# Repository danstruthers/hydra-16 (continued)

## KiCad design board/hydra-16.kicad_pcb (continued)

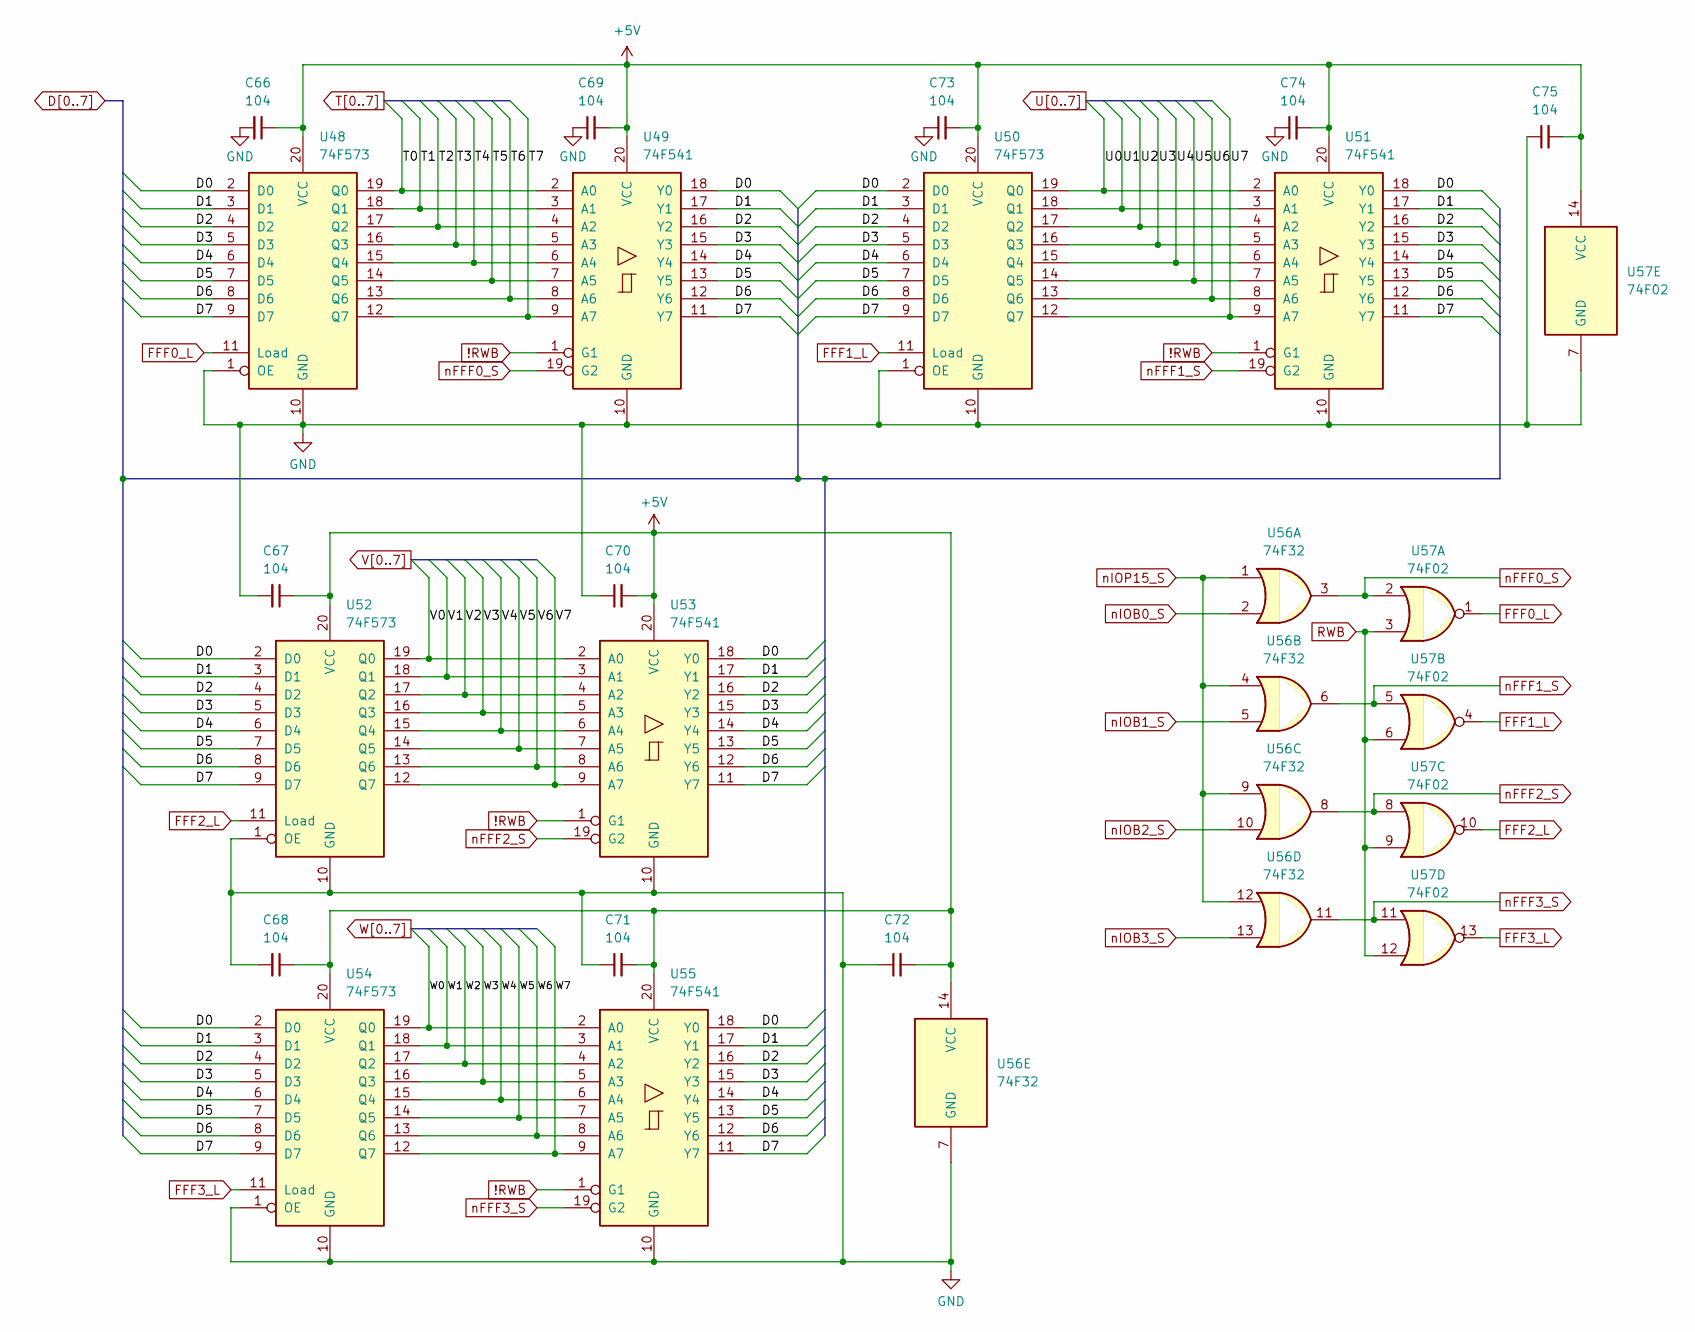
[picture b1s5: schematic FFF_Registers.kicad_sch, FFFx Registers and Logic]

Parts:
C66, C67, C68, C69, C70, C71, C72, C73, C74, C75: 104; C_Disc_D5.0mm_W2.5mm_P5.00mm
U48, U50, U52, U54: 74F573; DIP-20_W7.62mm_Socket_LongPads
U49, U51, U53, U55: 74F541; DIP-20_W7.62mm_Socket_LongPads
U56: 74F32; DIP-14_W7.62mm_Socket_LongPads
U57: 74F02; DIP-14_W7.62mm_Socket_LongPads

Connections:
!RWB: U49.1 (G1), U51.1 (G1), U53.1 (G1), U55.1 (G1); also elsewhere on the board
+5V: C66.1, C67.1, C68.1, C69.2, C70.2, C71.2, C72.2, C73.2, C74.2, C75.2, U48.20 (VCC), U49.20 (VCC), U50.20 (VCC), U51.20 (VCC), U52.20 (VCC), U53.20 (VCC), U54.20 (VCC), U55.20 (VCC), U56.14 (VCC), U57.14 (VCC); also elsewhere on the board
D0: U48.2 (D0), U49.18 (Y0), U50.2 (D0), U51.18 (Y0), U52.2 (D0), U53.18 (Y0), U54.2 (D0), U55.18 (Y0); also elsewhere on the board
D1: U48.3 (D1), U49.17 (Y1), U50.3 (D1), U51.17 (Y1), U52.3 (D1), U53.17 (Y1), U54.3 (D1), U55.17 (Y1); also elsewhere on the board
D2: U48.4 (D2), U49.16 (Y2), U50.4 (D2), U51.16 (Y2), U52.4 (D2), U53.16 (Y2), U54.4 (D2), U55.16 (Y2); also elsewhere on the board
D3: U48.5 (D3), U49.15 (Y3), U50.5 (D3), U51.15 (Y3), U52.5 (D3), U53.15 (Y3), U54.5 (D3), U55.15 (Y3); also elsewhere on the board
D4: U48.6 (D4), U49.14 (Y4), U50.6 (D4), U51.14 (Y4), U52.6 (D4), U53.14 (Y4), U54.6 (D4), U55.14 (Y4); also elsewhere on the board
D5: U48.7 (D5), U49.13 (Y5), U50.7 (D5), U51.13 (Y5), U52.7 (D5), U53.13 (Y5), U54.7 (D5), U55.13 (Y5); also elsewhere on the board
D6: U48.8 (D6), U49.12 (Y6), U50.8 (D6), U51.12 (Y6), U52.8 (D6), U53.12 (Y6), U54.8 (D6), U55.12 (Y6); also elsewhere on the board
D7: U48.9 (D7), U49.11 (Y7), U50.9 (D7), U51.11 (Y7), U52.9 (D7), U53.11 (Y7), U54.9 (D7), U55.11 (Y7); also elsewhere on the board
FFF0_L: U48.11 (Load), U57.1
FFF1_L: U50.11 (Load), U57.4
FFF2_L: U52.11 (Load), U57.10
FFF3_L: U54.11 (Load), U57.13
GND: C66.2, C67.2, C68.2, C69.1, C70.1, C71.1, C72.1, C73.1, C74.1, C75.1, U48.1 (OE), U48.10 (GND), U49.10 (GND), U50.1 (OE), U50.10 (GND), U51.10 (GND), U52.1 (OE), U52.10 (GND), U53.10 (GND), U54.1 (OE), U54.10 (GND), U55.10 (GND), U56.7 (GND), U57.7 (GND); also elsewhere on the board
RWB: U57.3, U57.6, U57.9, U57.12; also elsewhere on the board
T0: U48.19 (Q0), U49.2 (A0); also elsewhere on the board
T1: U48.18 (Q1), U49.3 (A1); also elsewhere on the board
T2: U48.17 (Q2), U49.4 (A2); also elsewhere on the board
T3: U48.16 (Q3), U49.5 (A3); also elsewhere on the board
T4: U48.15 (Q4), U49.6 (A4)
T5: U48.14 (Q5), U49.7 (A5)
T6: U48.13 (Q6), U49.8 (A6)
T7: U48.12 (Q7), U49.9 (A7)
U0: U50.19 (Q0), U51.2 (A0); also elsewhere on the board
U1: U50.18 (Q1), U51.3 (A1); also elsewhere on the board
U2: U50.17 (Q2), U51.4 (A2); also elsewhere on the board
U3: U50.16 (Q3), U51.5 (A3); also elsewhere on the board
U4: U50.15 (Q4), U51.6 (A4)
U5: U50.14 (Q5), U51.7 (A5)
U6: U50.13 (Q6), U51.8 (A6)
U7: U50.12 (Q7), U51.9 (A7)
V0: U52.19 (Q0), U53.2 (A0); also elsewhere on the board
V1: U52.18 (Q1), U53.3 (A1); also elsewhere on the board
V2: U52.17 (Q2), U53.4 (A2); also elsewhere on the board
V3: U52.16 (Q3), U53.5 (A3); also elsewhere on the board
V4: U52.15 (Q4), U53.6 (A4)
V5: U52.14 (Q5), U53.7 (A5)
V6: U52.13 (Q6), U53.8 (A6)
V7: U52.12 (Q7), U53.9 (A7)
W0: U54.19 (Q0), U55.2 (A0); also elsewhere on the board
W1: U54.18 (Q1), U55.3 (A1); also elsewhere on the board
W2: U54.17 (Q2), U55.4 (A2); also elsewhere on the board
W3: U54.16 (Q3), U55.5 (A3); also elsewhere on the board
W4: U54.15 (Q4), U55.6 (A4); also elsewhere on the board
W5: U54.14 (Q5), U55.7 (A5); also elsewhere on the board
W6: U54.13 (Q6), U55.8 (A6)
W7: U54.12 (Q7), U55.9 (A7)
nFFF0_S: U49.19 (G2), U56.3, U57.2
nFFF1_S: U51.19 (G2), U56.6, U57.5
nFFF2_S: U53.19 (G2), U56.8, U57.8
nFFF3_S: U55.19 (G2), U56.11, U57.11
nIOB0_S: U56.2; also elsewhere on the board
nIOB1_S: U56.5; also elsewhere on the board
nIOB2_S: U56.10; also elsewhere on the board
nIOB3_S: U56.13; also elsewhere on the board
nIOP15_S: U56.1, U56.4, U56.9, U56.12; also elsewhere on the board

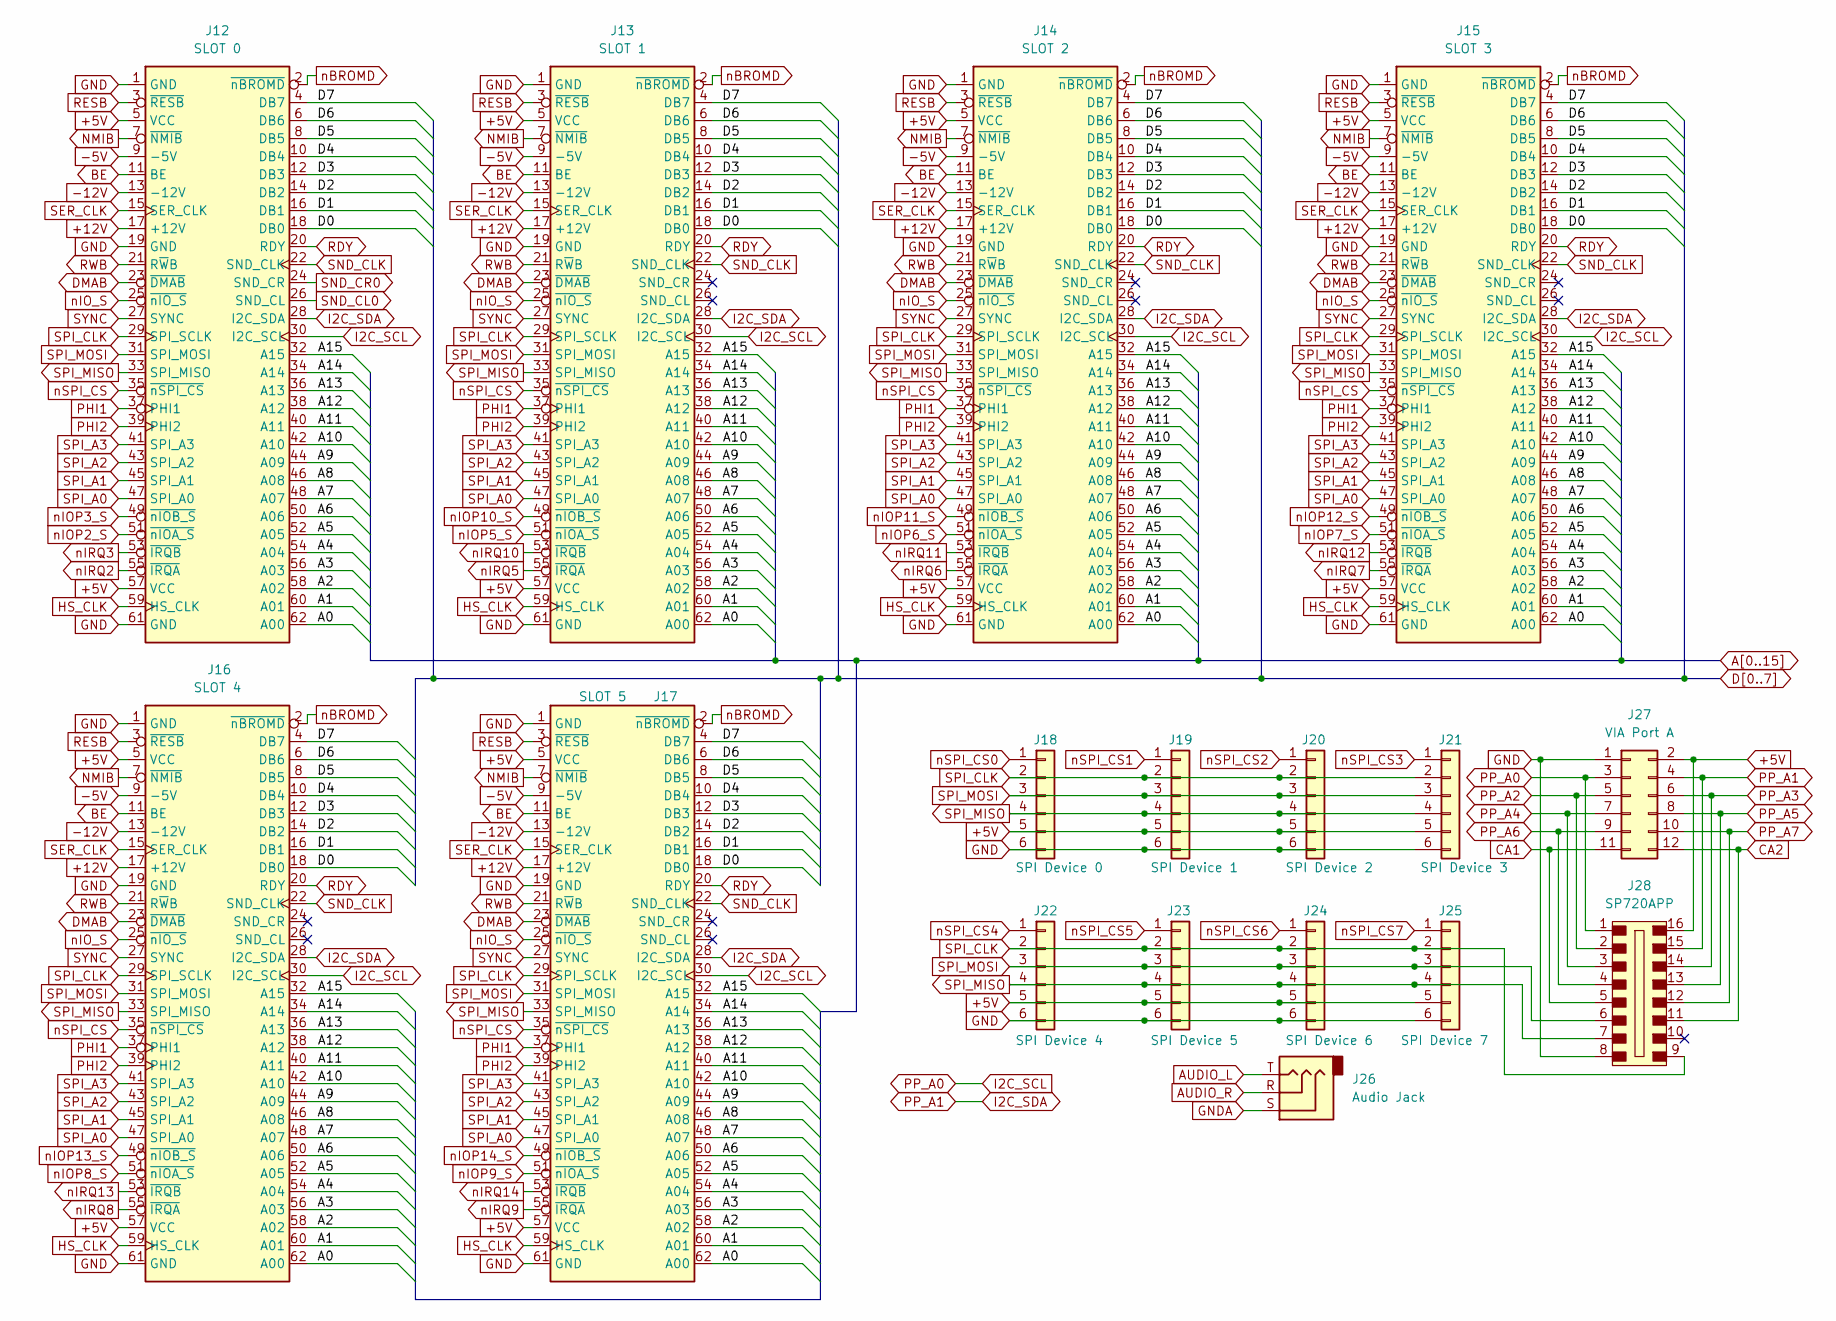
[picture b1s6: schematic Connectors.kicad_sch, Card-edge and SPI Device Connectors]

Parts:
J12: SLOT 0; TE_7-5530843-0
J13: SLOT 1; TE_7-5530843-0
J14: SLOT 2; TE_7-5530843-0
J15: SLOT 3; TE_7-5530843-0
J16: SLOT 4; TE_7-5530843-0
J17: SLOT 5; TE_7-5530843-0
J18: SPI Device 0; PinSocket_1x06_P2.54mm_Vertical
J19: SPI Device 1; PinSocket_1x06_P2.54mm_Vertical
J20: SPI Device 2; PinSocket_1x06_P2.54mm_Vertical
J21: SPI Device 3; PinSocket_1x06_P2.54mm_Vertical
J22: SPI Device 4; PinSocket_1x06_P2.54mm_Vertical
J23: SPI Device 5; PinSocket_1x06_P2.54mm_Vertical
J24: SPI Device 6; PinSocket_1x06_P2.54mm_Vertical
J25: SPI Device 7; PinSocket_1x06_P2.54mm_Vertical
J26: Audio Jack; Jack_3.5mm_CUI_SJ1-3525N_Horizontal
J27: VIA Port A; PinHeader_2x06_P2.54mm_Vertical
J28: SP720APP; DIP-16_W7.62mm_Socket_LongPads; MPN A 16-LC-TT; Digi-Key_PN AE9992-ND

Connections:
+5V: J12.5 (VCC), J12.57 (VCC), J13.5 (VCC), J13.57 (VCC), J14.5 (VCC), J14.57 (VCC), J15.5 (VCC), J15.57 (VCC), J16.5 (VCC), J16.57 (VCC), J17.5 (VCC), J17.57 (VCC), J18.5, J19.5, J20.5, J21.5, J22.5, J23.5, J24.5, J25.5, J27.2, J28.16; also elsewhere on the board
+12V: J12.17 (+12V), J13.17 (+12V), J14.17 (+12V), J15.17 (+12V), J16.17 (+12V), J17.17 (+12V); also elsewhere on the board
-5V: J12.9 (-5V), J13.9 (-5V), J14.9 (-5V), J15.9 (-5V), J16.9 (-5V), J17.9 (-5V); also elsewhere on the board
-12V: J12.13 (-12V), J13.13 (-12V), J14.13 (-12V), J15.13 (-12V), J16.13 (-12V), J17.13 (-12V); also elsewhere on the board
A0: J12.62 (A00), J13.62 (A00), J14.62 (A00), J15.62 (A00), J16.62 (A00), J17.62 (A00); also elsewhere on the board
A1: J12.60 (A01), J13.60 (A01), J14.60 (A01), J15.60 (A01), J16.60 (A01), J17.60 (A01); also elsewhere on the board
A2: J12.58 (A02), J13.58 (A02), J14.58 (A02), J15.58 (A02), J16.58 (A02), J17.58 (A02); also elsewhere on the board
A3: J12.56 (A03), J13.56 (A03), J14.56 (A03), J15.56 (A03), J16.56 (A03), J17.56 (A03); also elsewhere on the board
A4: J12.54 (A04), J13.54 (A04), J14.54 (A04), J15.54 (A04), J16.54 (A04), J17.54 (A04); also elsewhere on the board
A5: J12.52 (A05), J13.52 (A05), J14.52 (A05), J15.52 (A05), J16.52 (A05), J17.52 (A05); also elsewhere on the board
A6: J12.50 (A06), J13.50 (A06), J14.50 (A06), J15.50 (A06), J16.50 (A06), J17.50 (A06); also elsewhere on the board
A7: J12.48 (A07), J13.48 (A07), J14.48 (A07), J15.48 (A07), J16.48 (A07), J17.48 (A07); also elsewhere on the board
A8: J12.46 (A08), J13.46 (A08), J14.46 (A08), J15.46 (A08), J16.46 (A08), J17.46 (A08); also elsewhere on the board
A9: J12.44 (A09), J13.44 (A09), J14.44 (A09), J15.44 (A09), J16.44 (A09), J17.44 (A09); also elsewhere on the board
A10: J12.42 (A10), J13.42 (A10), J14.42 (A10), J15.42 (A10), J16.42 (A10), J17.42 (A10); also elsewhere on the board
A11: J12.40 (A11), J13.40 (A11), J14.40 (A11), J15.40 (A11), J16.40 (A11), J17.40 (A11); also elsewhere on the board
A12: J12.38 (A12), J13.38 (A12), J14.38 (A12), J15.38 (A12), J16.38 (A12), J17.38 (A12); also elsewhere on the board
A13: J12.36 (A13), J13.36 (A13), J14.36 (A13), J15.36 (A13), J16.36 (A13), J17.36 (A13); also elsewhere on the board
A14: J12.34 (A14), J13.34 (A14), J14.34 (A14), J15.34 (A14), J16.34 (A14), J17.34 (A14); also elsewhere on the board
A15: J12.32 (A15), J13.32 (A15), J14.32 (A15), J15.32 (A15), J16.32 (A15), J17.32 (A15); also elsewhere on the board
AUDIO_L: J26.T; also elsewhere on the board
AUDIO_R: J26.R; also elsewhere on the board
BE: J12.11 (BE), J13.11 (BE), J14.11 (BE), J15.11 (BE), J16.11 (BE), J17.11 (BE); also elsewhere on the board
CA1: J27.11, J28.5; also elsewhere on the board
CA2: J27.12, J28.11; also elsewhere on the board
D0: J12.18 (DB0), J13.18 (DB0), J14.18 (DB0), J15.18 (DB0), J16.18 (DB0), J17.18 (DB0); also elsewhere on the board
D1: J12.16 (DB1), J13.16 (DB1), J14.16 (DB1), J15.16 (DB1), J16.16 (DB1), J17.16 (DB1); also elsewhere on the board
D2: J12.14 (DB2), J13.14 (DB2), J14.14 (DB2), J15.14 (DB2), J16.14 (DB2), J17.14 (DB2); also elsewhere on the board
D3: J12.12 (DB3), J13.12 (DB3), J14.12 (DB3), J15.12 (DB3), J16.12 (DB3), J17.12 (DB3); also elsewhere on the board
D4: J12.10 (DB4), J13.10 (DB4), J14.10 (DB4), J15.10 (DB4), J16.10 (DB4), J17.10 (DB4); also elsewhere on the board
D5: J12.8 (DB5), J13.8 (DB5), J14.8 (DB5), J15.8 (DB5), J16.8 (DB5), J17.8 (DB5); also elsewhere on the board
D6: J12.6 (DB6), J13.6 (DB6), J14.6 (DB6), J15.6 (DB6), J16.6 (DB6), J17.6 (DB6); also elsewhere on the board
D7: J12.4 (DB7), J13.4 (DB7), J14.4 (DB7), J15.4 (DB7), J16.4 (DB7), J17.4 (DB7); also elsewhere on the board
DMAB: J12.23 (~DMAB), J13.23 (~DMAB), J14.23 (~DMAB), J15.23 (~DMAB), J16.23 (~DMAB), J17.23 (~DMAB); also elsewhere on the board
GND: J12.1 (GND), J12.19 (GND), J12.61 (GND), J13.1 (GND), J13.19 (GND), J13.61 (GND), J14.1 (GND), J14.19 (GND), J14.61 (GND), J15.1 (GND), J15.19 (GND), J15.61 (GND), J16.1 (GND), J16.19 (GND), J16.61 (GND), J17.1 (GND), J17.19 (GND), J17.61 (GND), J18.6, J19.6, J20.6, J21.6, J22.6, J23.6, J24.6, J25.6, J27.1, J28.8; also elsewhere on the board
GNDA: J26.S; also elsewhere on the board
HS_CLK: J12.59 (HS_CLK), J13.59 (HS_CLK), J14.59 (HS_CLK), J15.59 (HS_CLK), J16.59 (HS_CLK), J17.59 (HS_CLK); also elsewhere on the board
I2C_SCL: J12.30 (I2C_SCL), J13.30 (I2C_SCL), J14.30 (I2C_SCL), J15.30 (I2C_SCL), J16.30 (I2C_SCL), J17.30 (I2C_SCL), J27.3, J28.1; also elsewhere on the board
I2C_SDA: J12.28 (I2C_SDA), J13.28 (I2C_SDA), J14.28 (I2C_SDA), J15.28 (I2C_SDA), J16.28 (I2C_SDA), J17.28 (I2C_SDA), J27.4, J28.15; also elsewhere on the board
NMIB: J12.7 (~NMIB), J13.7 (~NMIB), J14.7 (~NMIB), J15.7 (~NMIB), J16.7 (~NMIB), J17.7 (~NMIB); also elsewhere on the board
PHI1: J12.37 (PHI1), J13.37 (PHI1), J14.37 (PHI1), J15.37 (PHI1), J16.37 (PHI1), J17.37 (PHI1); also elsewhere on the board
PHI2: J12.39 (PHI2), J13.39 (PHI2), J14.39 (PHI2), J15.39 (PHI2), J16.39 (PHI2), J17.39 (PHI2); also elsewhere on the board
PP_A2: J27.5, J28.2; also elsewhere on the board
PP_A3: J27.6, J28.14; also elsewhere on the board
PP_A4: J27.7, J28.3; also elsewhere on the board
PP_A5: J27.8, J28.13; also elsewhere on the board
PP_A6: J27.9, J28.4; also elsewhere on the board
PP_A7: J27.10, J28.12; also elsewhere on the board
RDY: J12.20 (RDY), J13.20 (RDY), J14.20 (RDY), J15.20 (RDY), J16.20 (RDY), J17.20 (RDY); also elsewhere on the board
RESB: J12.3 (~RESB), J13.3 (~RESB), J14.3 (~RESB), J15.3 (~RESB), J16.3 (~RESB), J17.3 (~RESB); also elsewhere on the board
RWB: J12.21 (R~WB), J13.21 (R~WB), J14.21 (R~WB), J15.21 (R~WB), J16.21 (R~WB), J17.21 (R~WB); also elsewhere on the board
SER_CLK: J12.15 (SER_CLK), J13.15 (SER_CLK), J14.15 (SER_CLK), J15.15 (SER_CLK), J16.15 (SER_CLK), J17.15 (SER_CLK); also elsewhere on the board
SND_CL0: J12.26 (SND_CL); also elsewhere on the board
SND_CLK: J12.22 (SND_CLK), J13.22 (SND_CLK), J14.22 (SND_CLK), J15.22 (SND_CLK), J16.22 (SND_CLK), J17.22 (SND_CLK); also elsewhere on the board
SND_CR0: J12.24 (SND_CR); also elsewhere on the board
SPI_A0: J12.47 (SPI_A0), J13.47 (SPI_A0), J14.47 (SPI_A0), J15.47 (SPI_A0), J16.47 (SPI_A0), J17.47 (SPI_A0); also elsewhere on the board
SPI_A1: J12.45 (SPI_A1), J13.45 (SPI_A1), J14.45 (SPI_A1), J15.45 (SPI_A1), J16.45 (SPI_A1), J17.45 (SPI_A1); also elsewhere on the board
SPI_A2: J12.43 (SPI_A2), J13.43 (SPI_A2), J14.43 (SPI_A2), J15.43 (SPI_A2), J16.43 (SPI_A2), J17.43 (SPI_A2); also elsewhere on the board
SPI_A3: J12.41 (SPI_A3), J13.41 (SPI_A3), J14.41 (SPI_A3), J15.41 (SPI_A3), J16.41 (SPI_A3), J17.41 (SPI_A3); also elsewhere on the board
SPI_CLK: J12.29 (SPI_SCLK), J13.29 (SPI_SCLK), J14.29 (SPI_SCLK), J15.29 (SPI_SCLK), J16.29 (SPI_SCLK), J17.29 (SPI_SCLK), J18.2, J19.2, J20.2, J21.2, J22.2, J23.2, J24.2, J25.2, J28.9; also elsewhere on the board
SPI_MISO: J12.33 (SPI_MISO), J13.33 (SPI_MISO), J14.33 (SPI_MISO), J15.33 (SPI_MISO), J16.33 (SPI_MISO), J17.33 (SPI_MISO), J18.4, J19.4, J20.4, J21.4, J22.4, J23.4, J24.4, J25.4, J28.7; also elsewhere on the board
SPI_MOSI: J12.31 (SPI_MOSI), J13.31 (SPI_MOSI), J14.31 (SPI_MOSI), J15.31 (SPI_MOSI), J16.31 (SPI_MOSI), J17.31 (SPI_MOSI), J18.3, J19.3, J20.3, J21.3, J22.3, J23.3, J24.3, J25.3, J28.6; also elsewhere on the board
SYNC: J12.27 (SYNC), J13.27 (SYNC), J14.27 (SYNC), J15.27 (SYNC), J16.27 (SYNC), J17.27 (SYNC); also elsewhere on the board
nBROMD: J12.2 (~nBROMD), J13.2 (~nBROMD), J14.2 (~nBROMD), J15.2 (~nBROMD), J16.2 (~nBROMD), J17.2 (~nBROMD); also elsewhere on the board
nIOP2_S: J12.51 (~nIOA_S); also elsewhere on the board
nIOP3_S: J12.49 (~nIOB_S); also elsewhere on the board
nIOP5_S: J13.51 (~nIOA_S); also elsewhere on the board
nIOP6_S: J14.51 (~nIOA_S); also elsewhere on the board
nIOP7_S: J15.51 (~nIOA_S); also elsewhere on the board
nIOP8_S: J16.51 (~nIOA_S); also elsewhere on the board
nIOP9_S: J17.51 (~nIOA_S); also elsewhere on the board
nIOP10_S: J13.49 (~nIOB_S); also elsewhere on the board
nIOP11_S: J14.49 (~nIOB_S); also elsewhere on the board
nIOP12_S: J15.49 (~nIOB_S); also elsewhere on the board
nIOP13_S: J16.49 (~nIOB_S); also elsewhere on the board
nIOP14_S: J17.49 (~nIOB_S); also elsewhere on the board
nIO_S: J12.25 (~nIO_S), J13.25 (~nIO_S), J14.25 (~nIO_S), J15.25 (~nIO_S), J16.25 (~nIO_S), J17.25 (~nIO_S); also elsewhere on the board
nIRQ2: J12.55 (~IRQA); also elsewhere on the board
nIRQ3: J12.53 (~IRQB); also elsewhere on the board
nIRQ5: J13.55 (~IRQA); also elsewhere on the board
nIRQ6: J14.55 (~IRQA); also elsewhere on the board
nIRQ7: J15.55 (~IRQA); also elsewhere on the board
nIRQ8: J16.55 (~IRQA); also elsewhere on the board
nIRQ9: J17.55 (~IRQA); also elsewhere on the board
nIRQ10: J13.53 (~IRQB); also elsewhere on the board
nIRQ11: J14.53 (~IRQB); also elsewhere on the board
nIRQ12: J15.53 (~IRQB); also elsewhere on the board
nIRQ13: J16.53 (~IRQB); also elsewhere on the board
nIRQ14: J17.53 (~IRQB); also elsewhere on the board
nSPI_CS: J12.35 (~nSPI_CS), J13.35 (~nSPI_CS), J14.35 (~nSPI_CS), J15.35 (~nSPI_CS), J16.35 (~nSPI_CS), J17.35 (~nSPI_CS); also elsewhere on the board
nSPI_CS0: J18.1; also elsewhere on the board
nSPI_CS1: J19.1; also elsewhere on the board
nSPI_CS2: J20.1; also elsewhere on the board
nSPI_CS3: J21.1; also elsewhere on the board
nSPI_CS4: J22.1; also elsewhere on the board
nSPI_CS5: J23.1; also elsewhere on the board
nSPI_CS6: J24.1; also elsewhere on the board
nSPI_CS7: J25.1; also elsewhere on the board

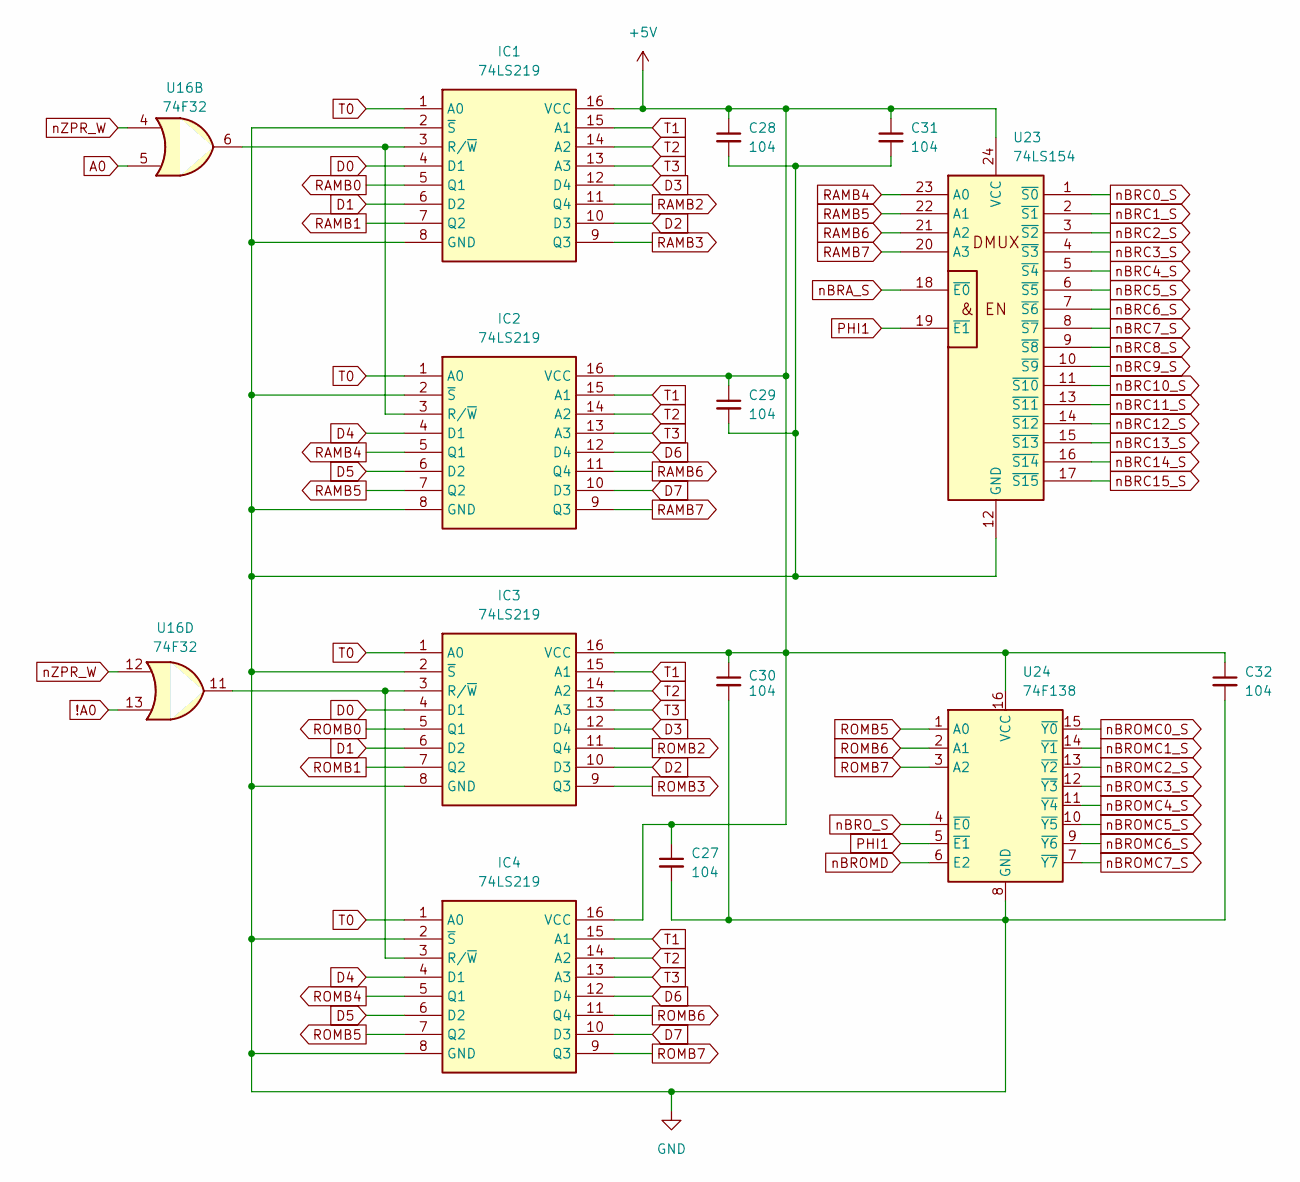
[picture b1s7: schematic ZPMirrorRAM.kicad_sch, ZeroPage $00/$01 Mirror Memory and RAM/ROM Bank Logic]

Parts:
C27, C28, C29, C30, C31, C32: 104; C_Disc_D5.0mm_W2.5mm_P5.00mm
IC1, IC2, IC3, IC4: 74LS219; DIP-16_W7.62mm_Socket_LongPads; Manufacturer_Part_Number SN74LS219AN
U16: 74F32; DIP-14_W7.62mm_Socket_LongPads
U23: 74LS154; DIP-24_W15.24mm_Socket_LongPads
U24: 74F138; DIP-16_W7.62mm_Socket_LongPads

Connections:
!A0: U16.13; also elsewhere on the board
+5V: C27.1, C28.1, C29.1, C30.1, C31.1, C32.1, IC1.16 (VCC), IC2.16 (VCC), IC3.16 (VCC), IC4.16 (VCC), U23.24 (VCC), U24.16 (VCC); also elsewhere on the board
A0: U16.5; also elsewhere on the board
D0: IC1.4 (D1), IC3.4 (D1); also elsewhere on the board
D1: IC1.6 (D2), IC3.6 (D2); also elsewhere on the board
D2: IC1.10 (D3), IC3.10 (D3); also elsewhere on the board
D3: IC1.12 (D4), IC3.12 (D4); also elsewhere on the board
D4: IC2.4 (D1), IC4.4 (D1); also elsewhere on the board
D5: IC2.6 (D2), IC4.6 (D2); also elsewhere on the board
D6: IC2.12 (D4), IC4.12 (D4); also elsewhere on the board
D7: IC2.10 (D3), IC4.10 (D3); also elsewhere on the board
GND: C27.2, C28.2, C29.2, C30.2, C31.2, C32.2, IC1.2 (~S), IC1.8 (GND), IC2.2 (~S), IC2.8 (GND), IC3.2 (~S), IC3.8 (GND), IC4.2 (~S), IC4.8 (GND), U23.12 (GND), U24.8 (GND); also elsewhere on the board
unnamed: IC1.3 (R/~W), IC2.3 (R/~W), U16.6
unnamed: IC3.3 (R/~W), IC4.3 (R/~W), U16.11
PHI1: U23.19 (~E1), U24.5 (~E1); also elsewhere on the board
RAMB0: IC1.5 (Q1); also elsewhere on the board
RAMB1: IC1.7 (Q2); also elsewhere on the board
RAMB2: IC1.11 (Q4); also elsewhere on the board
RAMB3: IC1.9 (Q3); also elsewhere on the board
RAMB4: IC2.5 (Q1), U23.23 (A0)
RAMB5: IC2.7 (Q2), U23.22 (A1)
RAMB6: IC2.11 (Q4), U23.21 (A2)
RAMB7: IC2.9 (Q3), U23.20 (A3)
ROMB0: IC3.5 (Q1); also elsewhere on the board
ROMB1: IC3.7 (Q2); also elsewhere on the board
ROMB2: IC3.11 (Q4); also elsewhere on the board
ROMB3: IC3.9 (Q3); also elsewhere on the board
ROMB4: IC4.5 (Q1); also elsewhere on the board
ROMB5: IC4.7 (Q2), U24.1 (A0)
ROMB6: IC4.11 (Q4), U24.2 (A1)
ROMB7: IC4.9 (Q3), U24.3 (A2)
T0: IC1.1 (A0), IC2.1 (A0), IC3.1 (A0), IC4.1 (A0); also elsewhere on the board
T1: IC1.15 (A1), IC2.15 (A1), IC3.15 (A1), IC4.15 (A1); also elsewhere on the board
T2: IC1.14 (A2), IC2.14 (A2), IC3.14 (A2), IC4.14 (A2); also elsewhere on the board
T3: IC1.13 (A3), IC2.13 (A3), IC3.13 (A3), IC4.13 (A3); also elsewhere on the board
nBRA_S: U23.18 (~E0); also elsewhere on the board
nBRC0_S: U23.1 (~S0); also elsewhere on the board
nBRC1_S: U23.2 (~S1); also elsewhere on the board
nBRC2_S: U23.3 (~S2); also elsewhere on the board
nBRC3_S: U23.4 (~S3); also elsewhere on the board
nBRC4_S: U23.5 (~S4); also elsewhere on the board
nBRC5_S: U23.6 (~S5); also elsewhere on the board
nBRC6_S: U23.7 (~S6); also elsewhere on the board
nBRC7_S: U23.8 (~S7); also elsewhere on the board
nBRC8_S: U23.9 (~S8); also elsewhere on the board
nBRC9_S: U23.10 (~S9); also elsewhere on the board
nBRC10_S: U23.11 (~S10); also elsewhere on the board
nBRC11_S: U23.13 (~S11); also elsewhere on the board
nBRC12_S: U23.14 (~S12); also elsewhere on the board
nBRC13_S: U23.15 (~S13); also elsewhere on the board
nBRC14_S: U23.16 (~S14); also elsewhere on the board
nBRC15_S: U23.17 (~S15); also elsewhere on the board
nBROMC0_S: U24.15 (~Y0); also elsewhere on the board
nBROMC1_S: U24.14 (~Y1); also elsewhere on the board
nBROMC2_S: U24.13 (~Y2); also elsewhere on the board
nBROMC3_S: U24.12 (~Y3); also elsewhere on the board
nBROMC4_S: U24.11 (~Y4); also elsewhere on the board
nBROMC5_S: U24.10 (~Y5); also elsewhere on the board
nBROMC6_S: U24.9 (~Y6); also elsewhere on the board
nBROMC7_S: U24.7 (~Y7); also elsewhere on the board
nBROMD: U24.6 (E2); also elsewhere on the board
nBRO_S: U24.4 (~E0); also elsewhere on the board
nZPR_W: U16.4, U16.12; also elsewhere on the board

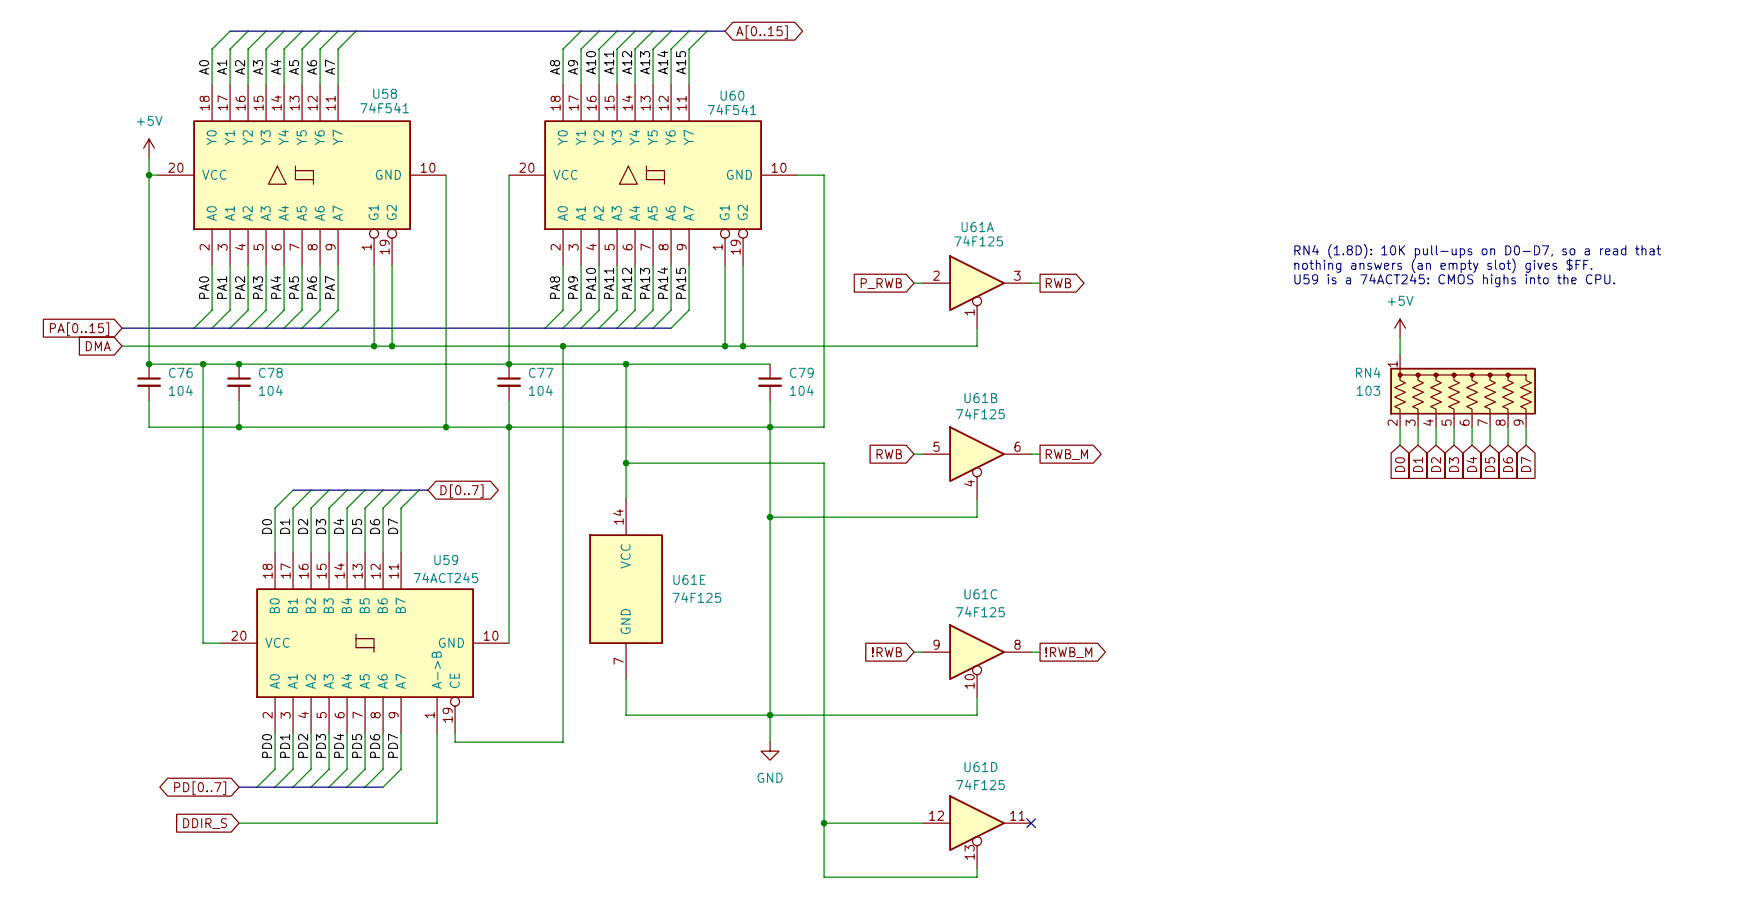
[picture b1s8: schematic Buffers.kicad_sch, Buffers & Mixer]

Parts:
C76, C77, C78, C79: 104; C_Disc_D5.0mm_W2.5mm_P5.00mm
RN4: 103; R_Array_SIP9
U58, U60: 74F541; DIP-20_W7.62mm_Socket_LongPads
U59: 74ACT245; DIP-20_W7.62mm_Socket_LongPads
U61: 74F125; DIP-14_W7.62mm_Socket_LongPads

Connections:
!RWB: U61.9; also elsewhere on the board
!RWB_M: U61.8; also elsewhere on the board
+5V: C76.1, C77.1, C78.1, C79.1, RN4.1 (common), U58.20 (VCC), U59.20 (VCC), U60.20 (VCC), U61.12, U61.13, U61.14 (VCC); also elsewhere on the board
A0: U58.18 (Y0); also elsewhere on the board
A1: U58.17 (Y1); also elsewhere on the board
A2: U58.16 (Y2); also elsewhere on the board
A3: U58.15 (Y3); also elsewhere on the board
A4: U58.14 (Y4); also elsewhere on the board
A5: U58.13 (Y5); also elsewhere on the board
A6: U58.12 (Y6); also elsewhere on the board
A7: U58.11 (Y7); also elsewhere on the board
A8: U60.18 (Y0); also elsewhere on the board
A9: U60.17 (Y1); also elsewhere on the board
A10: U60.16 (Y2); also elsewhere on the board
A11: U60.15 (Y3); also elsewhere on the board
A12: U60.14 (Y4); also elsewhere on the board
A13: U60.13 (Y5); also elsewhere on the board
A14: U60.12 (Y6); also elsewhere on the board
A15: U60.11 (Y7); also elsewhere on the board
D0: RN4.2 (R1), U59.18 (B0); also elsewhere on the board
D1: RN4.3 (R2), U59.17 (B1); also elsewhere on the board
D2: RN4.4 (R3), U59.16 (B2); also elsewhere on the board
D3: RN4.5 (R4), U59.15 (B3); also elsewhere on the board
D4: RN4.6 (R5), U59.14 (B4); also elsewhere on the board
D5: RN4.7 (R6), U59.13 (B5); also elsewhere on the board
D6: RN4.8 (R7), U59.12 (B6); also elsewhere on the board
D7: RN4.9 (R8), U59.11 (B7); also elsewhere on the board
DDIR_S: U59.1 (A->B); also elsewhere on the board
DMA: U58.1 (G1), U58.19 (G2), U59.19 (CE), U60.1 (G1), U60.19 (G2), U61.1; also elsewhere on the board
GND: C76.2, C77.2, C78.2, C79.2, U58.10 (GND), U59.10 (GND), U60.10 (GND), U61.4, U61.7 (GND), U61.10; also elsewhere on the board
PA0: U58.2 (A0); also elsewhere on the board
PA1: U58.3 (A1); also elsewhere on the board
PA2: U58.4 (A2); also elsewhere on the board
PA3: U58.5 (A3); also elsewhere on the board
PA4: U58.6 (A4); also elsewhere on the board
PA5: U58.7 (A5); also elsewhere on the board
PA6: U58.8 (A6); also elsewhere on the board
PA7: U58.9 (A7); also elsewhere on the board
PA8: U60.2 (A0); also elsewhere on the board
PA9: U60.3 (A1); also elsewhere on the board
PA10: U60.4 (A2); also elsewhere on the board
PA11: U60.5 (A3); also elsewhere on the board
PA12: U60.6 (A4); also elsewhere on the board
PA13: U60.7 (A5); also elsewhere on the board
PA14: U60.8 (A6); also elsewhere on the board
PA15: U60.9 (A7); also elsewhere on the board
PD0: U59.2 (A0); also elsewhere on the board
PD1: U59.3 (A1); also elsewhere on the board
PD2: U59.4 (A2); also elsewhere on the board
PD3: U59.5 (A3); also elsewhere on the board
PD4: U59.6 (A4); also elsewhere on the board
PD5: U59.7 (A5); also elsewhere on the board
PD6: U59.8 (A6); also elsewhere on the board
PD7: U59.9 (A7); also elsewhere on the board
P_RWB: U61.2; also elsewhere on the board
RWB: U61.3, U61.5; also elsewhere on the board
RWB_M: U61.6; also elsewhere on the board

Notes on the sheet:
RN4 (1.8D): 10K pull-ups on D0-D7, so a read that nothing answers (an empty slot) gives $FF. U59 is a 74ACT245: CMOS highs into the CPU.
